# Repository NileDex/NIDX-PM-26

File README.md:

<!-- boardrepo-badge:v1 -->

<!-- /boardrepo-badge:v1 -->

# NIDX-PM-26: Dual-Channel MCU Power Management & Protection Module

**NIDX-PM-26** is a dual-channel power distribution, circuit protection, and telemetry module designed by **NileDex** for microcontrollers (MCUs), development boards (ESP32, STM32, Arduino, Raspberry Pi), and sensitive embedded systems.

The module provides active reverse polarity protection, programmable current-limiting switches with hardware fault flags, and high-precision 20-bit digital power monitoring (voltage, current, power, and energy accumulation) over a shared I2C bus.

---

## Key Features

- **Dual Independent Channels**: Two isolated power paths (Channel 1 & Channel 2) capable of operating from independent or common supply rails.
- **Active Reverse Polarity Protection**: Low-$R_{DS(on)}$ P-Channel MOSFETs (`AO3401A`) prevent reverse-voltage damage with negligible voltage drop compared to traditional Schottky diodes.
- **Precision Electronic Current Limiting & Load Switching**: Integrated Texas Instruments `TPS2553DBVR` power switches with programmable current limit threshold, fast short-circuit response, and thermal shutdown with auto-recovery.
  - Set to **~500 mA** per channel ($R_{ILIM} = 47\text{ k}\Omega$), adjustable from 75 mA to 1.7 A by changing resistor values.
- **High-Resolution Power Telemetry (INA228)**: Dual 20-bit Delta-Sigma ADCs monitoring bus voltage, shunt voltage, bidirectional current, and power consumption with high accuracy.
- **Hardware Fault & Alert Reporting**: Dedicated open-drain `FAULT` (TPS2553) and programmable `ALERT` (INA228) outputs broken out for direct microcontroller interrupt handling.
- **Flexible Logic Level Compatibility**: On-board I2C pull-up resistors are tied to an external `VDD_I2C` pin, allowing seamless operation with 1.8V, 3.3V, or 5V microcontroller logic.

---

## System Architecture

```
                  CHANNEL 1
J1 Pin 1 ──► [Q1: AO3401A] ──► [U1: TPS2553] ──► [R1: 0.1Ω Shunt] ──► J2 Pin 1
 (VIN1)     (Reverse Protect)  (Current Limit)             │          (VOUT1)
                                      │                    ▼
                                      │              [U2: INA228]
                                      ▼             (20-bit I2C: 0x40)
                              FAULT1 ──► J4 Pin 7          │
                                                    ALERT1 ──► J4 Pin 5

                  CHANNEL 2
J1 Pin 2 ──► [Q2: AO3401A] ──► [U4: TPS2553] ──► [R2: 0.1Ω Shunt] ──► J2 Pin 2
 (VIN2)     (Reverse Protect)  (Current Limit)             │          (VOUT2)
                                      │                    ▼
                                      │              [U3: INA228]
                                      ▼             (20-bit I2C: 0x44)
                              FAULT2 ──► J4 Pin 8          │
                                                    ALERT2 ──► J4 Pin 6

                  CONTROL & I2C INTERFACE (J4)
J4 Pin 1 ──► VDD_I2C (Pull-up Reference: 1.8V - 5V)
J4 Pin 2 ──► GND
J4 Pin 3 ──► SDA (Shared I2C Data bus, 4.7kΩ pull-up R3)
J4 Pin 4 ──► SCL (Shared I2C Clock bus, 4.7kΩ pull-up R4)
```

---

## Detailed Circuit Design

### 1. Reverse Polarity Protection (`Q1`, `Q2`)
- **Part**: Alpha & Omega `AO3401A` (-30V, -4.0A, SOT-23 P-Channel MOSFET).
- **Function**: Gate tied to GND; Source connects to the circuit rail, and Drain connects to the input power connector.
- **Behavior**: If reverse voltage is applied ($V_{IN} < 0\text{V}$), $V_{GS} > 0\text{V}$ keeps the MOSFET off, completely blocking reverse current. When correct polarity is applied, the channel turns fully on with $R_{DS(on)} \approx 44\text{ m}\Omega$, minimizing power loss and voltage sag.

### 2. Overcurrent Protection & Load Switching (`U1`, `U4`)
- **Part**: Texas Instruments `TPS2553DBVR` (SOT-23-6).
- **Operation**: Active-high enable (`EN`) tied to `IN` for automatic power pass-through.
- **Current Limit Programming**:
  The trip current is set by $R_{ILIM}$ resistors `R5_LM1` and `R6_LM1` ($47\text{ k}\Omega$):
  $$I_{OS(typ)} \approx \frac{24212}{(R_{ILIM})^{0.985}} \approx \frac{24212}{(47000)^{0.985}} \approx 595\text{ mA}$$
  (Nominal continuous working current: $\sim 500\text{ mA}$).
- **Fault Detection**: The active-low open-drain `FAULT` pin signals over-current or thermal shutdown events to the host MCU via `J4`.

### 3. Precision Current & Power Sensing (`U2`, `U3`)
- **Part**: Texas Instruments `INA228` (TSSOP-10).
- **Resolution**: 20-bit Delta-Sigma ADC with $1\text{ }\mu\text{V}$ shunt voltage LSB and $195.3125\text{ }\mu\text{V}$ bus voltage LSB.
- **Current Sense Resistors**: `R1`, `R2` = $0.1\text{ }\Omega$ ($100\text{ m}\Omega$, 0805 SMD package).
- **I2C Addressing**:
  | Channel | IC Designator | A1 Pin | A0 Pin | 7-bit I2C Address (Hex) | 7-bit I2C Address (Binary) |
  |---------|---------------|--------|--------|-------------------------|----------------------------|
  | **Ch 1** | `U2` | GND | GND | `0x40` | `1000000b` |
  | **Ch 2** | `U3` | VS (Rail) | GND | `0x44` | `1000100b` |

- **Alert Pins**: Open-drain output asserted when programmed power, current, or voltage limits are exceeded.

---

## Connector Pinouts

### J1: Input Power Connector (1x03 Pin Header, 1.00mm Pitch)
| Pin # | Silkscreen | Signal | Type | Description |
|:-----:|:----------:|:------:|:----:|:------------|
| 1 | `+5v` | `VIN1` | Power Input | Channel 1 Input Voltage (+2.5V to +6.5V) |
| 2 | `3v3` | `VIN2` | Power Input | Channel 2 Input Voltage (+2.5V to +6.5V) |
| 3 | `GND` | `GND` | Ground | Common Power Ground |

### J2: Output Power Connector (1x03 Pin Header, 1.00mm Pitch)
| Pin # | Silkscreen | Signal | Type | Description |
|:-----:|:----------:|:------:|:----:|:------------|
| 1 | `+5v` | `VOUT1` | Power Output | Channel 1 Protected & Monitored Power Output |
| 2 | `3v3` | `VOUT2` | Power Output | Channel 2 Protected & Monitored Power Output |
| 3 | `GND` | `GND` | Ground | Common Power Ground |

### J4: Telemetry & Diagnostics Interface (1x08 Pin Header, 1.00mm Pitch)
| Pin # | Silkscreen | Signal | Type | Description |
|:-----:|:----------:|:------:|:----:|:------------|
| 1 | `VIO` | `VDD_I2C` | Power Input | I2C pull-up reference voltage (1.8V, 3.3V, or 5V MCU logic) |
| 2 | `GND` | `GND` | Ground | System Ground reference for digital signals |
| 3 | `SDA` | `SDA` | I/O | I2C Data line (pulled up via `R3` $4.7\text{ k}\Omega$ to `VIO`) |
| 4 | `SCL` | `SCL` | Input | I2C Clock line (pulled up via `R4` $4.7\text{ k}\Omega$ to `VIO`) |
| 5 | `ALRT` | `ALERT1` | Output (OD) | Channel 1 INA228 programmable threshold alert |
| 6 | `ALRT` | `ALERT2` | Output (OD) | Channel 2 INA228 programmable threshold alert |
| 7 | `FAULT` | `FAULT1` | Output (OD) | Channel 1 TPS2553 fault flag (Active Low) |
| 8 | `FAULT` | `FAULT2` | Output (OD) | Channel 2 TPS2553 fault flag (Active Low) |

---

## Electrical Specifications

| Parameter | Min | Typical | Max | Unit | Notes |
|:----------|:---:|:-------:|:---:|:----:|:------|
| **Input Voltage ($V_{IN}$)** | 2.5 | 3.3 / 5.0 | 6.5 | V | Limited by TPS2553 supply range |
| **Current Limit Threshold ($I_{LIMIT}$)** | 450 | 500 | 600 | mA | Configured by $47\text{ k}\Omega$ $R_{ILIM}$ resistors |
| **Current Sense Resistance ($R_{SHUNT}$)** | - | 0.1 | - | $\Omega$ | Tolerance 1%, 0805 package |
| **Reverse Polarity Voltage Blocking** | - | - | -30 | V | $V_{DS(max)}$ of AO3401A |
| **I2C Bus Speed** | 10 | 400 | 1000 | kHz | Standard, Fast, and Fast-Mode+ supported |
| **Digital Logic Voltage (`VDD_I2C`)** | 1.8 | 3.3 | 5.5 | V | Feeds pull-ups `R3` and `R4` |
| **Operating Ambient Temperature** | -40 | +25 | +85 | °C | Industrial rated components |

---

## Bill of Materials (BOM)

| Designator | Value / Part Number | Description | Footprint / Package |
|:-----------|:--------------------|:------------|:--------------------|
| **U1, U4** | `TPS2553DBVR` | Precision Adj. Current-Limited Switch | SOT-23-6 |
| **U2, U3** | `INA228` | 20-bit Current/Power/Energy Monitor | TSSOP-10 (3x3mm, 0.5mm pitch) |
| **Q1, Q2** | `AO3401A` | P-Channel MOSFET (-30V, -4.0A) | SOT-23-3 |
| **R1, R2** | `0.1` ($100\text{ m}\Omega$) | Current Shunt Resistor, 1% | SMD 0805 |
| **R3, R4** | `4.7k` | I2C Bus Pull-Up Resistors | SMD 0805 |
| **R5_LM1, R6_LM1** | `47k` | Current Limit Set Resistors (TPS2553) | SMD 0805 |
| **C1, C2, C3, C4** | `100n` ($0.1\text{ }\mu\text{F}$) | Ceramic Decoupling Capacitors, 50V | SMD 0805 |
| **C5, C6, C7, C8** | `10u` ($10\text{ }\mu\text{F}$) | Ceramic Bulk Filter Capacitors, 16V/25V | SMD 0805 |
| **J1, J2** | `Conn_01x03` | 3-pin Power Input/Output Header | 1x03 Pin Header (1.00mm pitch) |
| **J4** | `Conn_01x08` | 8-pin Diagnostics & Telemetry Header | 1x08 Pin Header (1.00mm pitch) |

---

## Firmware Integration Example (Arduino / C++)

```cpp
#include <Wire.h>

// I2C Addresses
#define INA228_CH1_ADDR 0x40
#define INA228_CH2_ADDR 0x44

// Pin Definitions on Host MCU
#define PIN_FAULT1 4
#define PIN_FAULT2 5
#define PIN_ALERT1 6
#define PIN_ALERT2 7

void setup() {
  Serial.begin(115200);
  Wire.begin();

  pinMode(PIN_FAULT1, INPUT_PULLUP);
  pinMode(PIN_FAULT2, INPUT_PULLUP);
  pinMode(PIN_ALERT1, INPUT_PULLUP);
  pinMode(PIN_ALERT2, INPUT_PULLUP);

  Serial.println("NIDX-PM-26 Initialized.");
}

void loop() {
  // Check for TPS2553 hardware fault (Active LOW)
  if (digitalRead(PIN_FAULT1) == LOW) {
    Serial.println("WARNING: Channel 1 Over-Current or Thermal Fault detected!");
  }
  if (digitalRead(PIN_FAULT2) == LOW) {
    Serial.println("WARNING: Channel 2 Over-Current or Thermal Fault detected!");
  }

  // Read voltage & current telemetry via I2C (INA228)
  readTelemetry(INA228_CH1_ADDR, "Channel 1");
  readTelemetry(INA228_CH2_ADDR, "Channel 2");

  delay(1000);
}

void readTelemetry(uint8_t address, const char* channelName) {
  // Read VBUS Register (0x05 for INA228)
  Wire.beginTransmission(address);
  Wire.write(0x05);
  if (Wire.endTransmission() == 0) {
    Wire.requestFrom(address, (uint8_t)3);
    if (Wire.available() >= 3) {
      uint32_t rawVbus = ((uint32_t)Wire.read() << 16) | ((uint32_t)Wire.read() << 8) | Wire.read();
      rawVbus >>= 4; // 20-bit data alignment
      float voltage = rawVbus * 195.3125e-6; // 195.3125 uV/LSB
      Serial.print(channelName);
      Serial.print(" Voltage: ");
      Serial.print(voltage, 3);
      Serial.println(" V");
    }
  }
}
```

---

## Repository Structure

```
mcu-protection/
├── .gitignore                     # Git ignore rules (schematics, netlists & temporary files ignored)
├── LICENSE                        # MIT License
├── README.md                      # Hardware documentation and wiring guide
├── mcu-protection.kicad_pro       # KiCad 10 project file
├── mcu-protection.kicad_pcb       # KiCad PCB layout
├── mcu-protection.png             # PCB 3D preview render
└── ERC.rpt                        # Electrical Rules Check report
```

---

## License

This project is licensed under the [MIT License](LICENSE).
Copyright (c) 2026 NileDex (NIDX-PM-26 Contributors).

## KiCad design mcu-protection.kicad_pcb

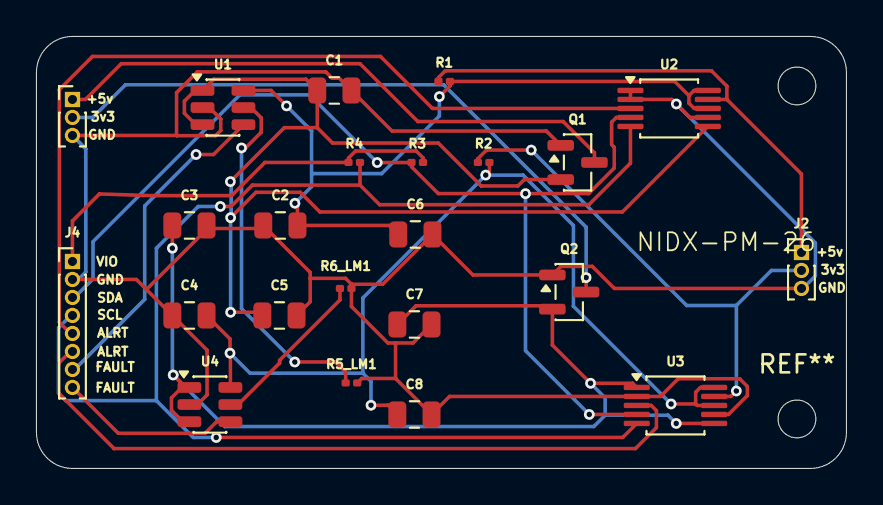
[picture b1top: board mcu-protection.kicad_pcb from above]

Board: 2 copper layers, 45.0 x 24.0 mm, 23 parts (0 on the bottom side), 18 nets.

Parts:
C1, C2, C3, C4: 100n; C_0805_2012Metric
C5, C6, C7, C8: 10u; C_0805_2012Metric
J1, J2: Conn_01x03; PinHeader_1x03_P1.00mm_Vertical
J4: Conn_01x08; PinHeader_1x08_P1.00mm_Vertical
Q1, Q2: AO3401A; SOT-23
R1, R2: 0.1; R_0201_0603Metric
R3, R4: 4.7k; R_0201_0603Metric
R5_LM1, R6_LM1: 47K; R_0201_0603Metric
U1, U4: TPS2553DBVR; SOT-23-6
U2, U3: INA228; TSSOP-10_3x3mm_P0.5mm

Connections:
GND: C1.2, C2.1, C3.2, C4.1, C5.2, C6.2, C7.2, C8.2, J1.3, J2.3, J4.2, Q1.1 (G), Q2.1 (G), R5_LM1.2, R6_LM1.2, U1.2 (GND), U2.1 (A1), U2.2 (A0), U2.7 (GND), U3.2 (A0), U3.7 (GND), U4.2 (GND)
unnamed: J1.1, Q1.3 (D)
unnamed: J1.2, Q2.3 (D)
unnamed: J2.1, R1.1, U2.9 (Vin-)
unnamed: J2.2, R2.1, U3.9 (Vin-)
unnamed: J4.1, R3.2, R4.1
unnamed: J4.3, R3.1, U2.4 (SDA), U3.4 (SDA)
unnamed: J4.4, R4.2, U2.5 (SCL), U3.5 (SCL)
unnamed: J4.5, U2.3 (~Alert)
unnamed: J4.6, U3.3 (~Alert)
unnamed: J4.7, U1.4 (~FAULT)
unnamed: J4.8, U4.4 (~FAULT)
unnamed: C1.1, C5.1, Q1.2 (S), U1.1 (IN), U1.3 (EN), U2.6 (VS)
unnamed: C3.1, C7.1, Q2.2 (S), U3.1 (A1), U3.6 (VS), U4.1 (IN), U4.3 (EN)
unnamed: R5_LM1.1, U1.5 (ILIM)
unnamed: C2.2, C6.1, R1.2, U1.6 (OUT), U2.8 (Vbus), U2.10 (Vin+)
unnamed: C4.2, C8.1, R2.2, U3.8 (Vbus), U3.10 (Vin+), U4.6 (OUT)
unnamed: R6_LM1.1, U4.5 (ILIM)
